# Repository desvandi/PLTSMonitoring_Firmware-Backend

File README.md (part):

# PLTS Monitoring — Firmware, Backend GAS, & Toolkit

**Firmware Version:** v1.9.3 · **Backend GAS:** WAVE-7+ · **License:** MIT
**Status:** Development (v1.9.x INA219 dynamic gain switching — hardware acceptance pending; v1.9.3 menutup REL-03/REL-04: build kini reproducible)
**Repositori kembar (PWA frontend):** [desvandi/PLTSMonitoring_PWA](https://github.com/desvandi/PLTSMonitoring_PWA)

---

## Daftar Isi

1. [Gambaran Proyek](#1-gambaran-proyek)
2. [Arsitektur Sistem](#2-arsitektur-sistem)
3. [Struktur Repositori](#3-struktur-repositori)
4. [Hardware Requirements](#4-hardware-requirements)
5. [Firmware v1.9.x — INA219 Dynamic Gain Switching](#5-firmware-v19x--ina219-dynamic-gain-switching)
6. [Panduan Deployment Lengkap](#6-panduan-deployment-lengkap)
7. [Konfigurasi Firmware](#7-konfigurasi-firmware)
8. [Backend Google Apps Script](#8-backend-google-apps-script)
9. [CI/CD Pipeline](#9-cicd-pipeline)
10. [Release Engineering](#10-release-engineering)
11. [Hardware Acceptance](#11-hardware-acceptance)
12. [Testing](#12-testing)
13. [Troubleshooting](#13-troubleshooting)
14. [Changelog](#14-changelog)

---

## 1. Gambaran Proyek

Proyek ini adalah sistem monitoring PLTS (Pembangkit Listrik Tenaga Surya) berbasis ESP32 untuk baterai 48V LiFePO4. Sistem mencakup telemetri lengkap (tegangan, arus, daya, SOC, suhu, BMS), alarm real-time, kontrol relay 8-channel, OTA update dengan signature verification, dan push notification.

### Dua Subsistem

| Subsistem | Fungsi | Komponen |
|-----------|--------|----------|
| **PLTS Monitor** (dasbor) | Telemetri → Google Apps Script → PWA Next.js; realtime MQTT opsional | `firmware/`, `firmware-generic/`, `code.gs/`, `scripts/` |
| **Push-Alarm MonitorIoT** | Alarm sensor via Web Push terenkripsi (VAPID + aes128gcm) | `push-alarm/` |

### Prinsip Inti

- **Never fabricate certainty** — setiap pengukuran membawa `value/unit/quality/source/timestamp`; sensor gagal → `null` (bukan `0`)
- **Fail-closed** — production build menolak konfigurasi tanpa signature/CA/allowlist
- **Immutable releases** — setiap release ditandatangani GPG + Ed25519, provenance binding machine-verifiable

---

## 2. Arsitektur Sistem

```
┌─────────────────────────────────────────────────────────────┐
│                     ESP32-WROOM-32                          │
│                                                             │
│  ┌──────────┐  ┌──────────┐  ┌──────────┐  ┌──────────┐   │
│  │ INA219   │  │ ADC GPIO │  │ SHT31    │  │ PCF8574  │   │
│  │ (Arus)   │  │ (Tegang) │  │ (Suhu)   │  │ (Relay)  │   │
│  └────┬─────┘  └────┬─────┘  └────┬─────┘  └────┬─────┘   │
│       │ I²C         │ ADC         │ I²C         │ I²C      │
│  ┌────┴─────────────┴─────────────┴─────────────┴────┐    │
│  │              Firmware v1.9.3                      │    │
│  │  • Dynamic PGA Switching (±80mV / ±160mV)        │    │
│  │  • Voltage Divider 190kΩ/10kΩ (20:1)             │    │
│  │  • 8-Channel Relay Controller (E-WAVE)           │    │
│  │  • Reproducible Build (deterministic identity)   │    │
│  │  • OTA Manager (Ed25519 + SHA-256)               │    │
│  │  • MQTT TLS / HTTPS telemetry                    │    │
│  └───────────────────┬──────────────────────────────┘    │
│                      │                                    │
└──────────────────────┼────────────────────────────────────┘
                       │
              ┌────────┴────────┐
              │   WiFi / MQTT   │
              └────────┬────────┘
                       │
          ┌────────────┴────────────┐
          │                         │
    ┌─────┴─────┐           ┌──────┴──────┐
    │  HTTPS    │           │   MQTT TLS  │
    │  POST     │           │  (opsional) │
    └─────┬─────┘           └──────┬──────┘
          │                        │
    ┌─────┴────────────────────────┴─────┐
    │     Google Apps Script (Backend)    │
    │  • Telemetry ingest (HMAC auth)     │
    │  • Google Sheets logging            │
    │  • Telegram alerts                 │
    │  • OTA command dispatch             │
    └─────────────┬───────────────────────┘
                  │
           ┌──────┴──────┐
           │  PWA (Vercel) │
           │  Next.js 16   │
           └───────────────┘
```

### Topologi Operasi

| Topologi | Transport | Backend | Use Case |
|----------|-----------|--------|----------|
| **A (Dasbor)** | HTTPS POST | Google Apps Script + Google Sheets | Standby/standalone tanpa internet real-time |
| **B (Realtime)** | MQTT TLS | Broker MQTT + PWA subscribe | Real-time dashboard dengan live updates |

---

## 3. Struktur Repositori

```
PLTSMonitoring_Firmware-Backend/
├── firmware/                    # Modular production firmware (v1.9.3)
│   ├── Core/                    #   Config.h, Types.h, Globals.h, Common.h
│   ├── Drivers/                 #   INA219, ADC, SHT31, ACS712, PCF8574, RTC
│   ├── Services/                #   OtaManager, RelayController, AlarmRegistry, dll
│   ├── Network/                 #   MQTT transport, telemetry publisher, OTA handler
│   ├── Web/                     #   HTTP server, REST handlers (status, OTA, config, dll)
│   ├── Storage/                 #   NVS config store, filesystem
│   ├── Utils/                   #   Crypto (Ed25519), CRC, I2C recovery, JSON
│   ├── AI/                      #   GasAdvisor (HMAC-signed AI insights)
│   ├── Comm/                    #   BMS protocols (CAN, Modbus RTU/TCP)
│   ├── firmware_v1.ino          #   Main entry point
│   ├── platformio.ini           #   Build configs: development, staging, production
│   └── partitions_ota_1mb5.csv  #   OTA partition table
│
├── firmware-generic/            # Generic firmware (ESP Web Tools flashing)
│   ├── src/
│   │   └── plts_firmware_v1.ino #   Single-file firmware (same features, simpler build)
│   ├── manifest.json            #   ESP Web Tools manifest (v1.9.3)
│   ├── platformio.ini
│   └── bin/                     #   CI-built binaries (gitignored)
│
├── code.gs/                     # Google Apps Script backend
│   └── Code.gs                  #   doPost handler, telemetry ingest, HMAC, OTA dispatch
│
├── push-alarm/                  # MonitorIoT Push-Alarm subsystem
│   ├── gas/                     #   GAS Web Push core (Code.gs, WebPushCore.gs)
│   ├── firmware/                #   Alarm firmware (MonitorIoT_Firmware.ino)
│   ├── tools/                   #   VAPID key gen, deploy config, audit tools
│   └── tests/                   #   Cross-audit, smoke, webpush-core tests
│
├── scripts/                     # Release engineering + testing
│   ├── sign_firmware.py         #   Ed25519 firmware signing
│   ├── generate_provenance.py   #   Release provenance (release.json, provenance.json)
│   ├── generate_canonical_manifest.py  # Schema 2.0 OTA manifest
│   ├── generate_provenance_binding.py  # Explicit provenance chain
│   ├── release_gate.py          #   Master release gate (strict mode)
│   ├── release_firmware_generic.py    # Generic tree release builder
│   ├── verify_tag_signature.py  #   GPG tag verification (P0-1)
│   ├── verify_hardware_acceptance.py  # HW acceptance gate (P0-2)
│   ├── verify_ota_evidence.py   #   OTA physical test gate
│   ├── verify_ina219_hardware_acceptance.py  # INA219 HW acceptance (v1.9.x)
│   ├── decode_ina219_config.py  #   INA219 register decoder (canonical)
│   ├── test_ina219_config_registers.py  # INA219 register unit test
│   ├── test_*.py / test_*.js    #   30+ test scripts (unit, property, contract, bench)
│   └── ...
│
├── docs/                        #   Hanya data fungsional (dibaca skrip/CI)
│   ├── hardware-revisions.json  #     Registry revisi hardware (verify_ota_evidence dkk.)
│   ├── hardware-acceptance/     #   Evidence + template verifikasi (release gate P0-2)
│   │   ├── v1.8.0.json          #     Filled-in evidence (verdict=PASS)
│   │   ├── v1.8.0.template.json #     Template v1.8.0
│   │   ├── v1.9.2.template.json #     Template v1.9.2
│   │   └── v1.9.3.template.json #     Template v1.9.3 (REL-03: SHA byte-exact evidence)
│   └── ota-physical-test/       #   Template uji fisik OTA (verify_ota_evidence)
│       ├── v1.8.0.template.json
│       └── v1.9.3.template.json
│
├── .github/workflows/
│   └── build-firmware.yml       #   CI: test → build → sign → gate → tag-verify → hw-verify → release
│
└── README.md                    # File ini
```

---

## 4. Hardware Requirements

### Komponen Utama

| Komponen | Spesifikasi | Fungsi |
|----------|-------------|--------|
| **ESP32-WROOM-32** | Dual-core 240MHz, 4MB Flash, WiFi+BT | Mikrokontroler utama |
| **INA219** | I²C 0x40, shunt 100A/75mV (R=0.75mΩ) | Pengukuran arus baterai (1A–150A) |
| **Shunt Resistor** | 100A/75mV (0.75mΩ) | Low-side current sensing |
| **Voltage Divider** | R1=190kΩ, R2=10kΩ (ratio 20:1) + 0.1µF cap | Pembacaan tegangan baterai 42–57.5V via ADC |
| **SHT31** | I²C, ±0.3°C, ±2%RH | Suhu + kelembaban ambient |
| **PCF8574** | I²C expander 8-bit | 8-channel relay control |
| **Relay Module** | 8-channel, active-LOW optocoupler | Kontrol beban PLTS |
| **Emergency Relay** | Active-LOW, normally-closed E-stop | Safety cutoff (hardware-level) |
| **ACS712-30A** (opsional) | ADC GPIO35 | Arus AC inverter |
| **PZEM-004T** (opsional) | Modbus RTU | Meter AC presisi |

### Wiring INA219 (Low-Side Sensing)

```
Baterai (+) ──────────────────────────────────────── Beban (+)
                                              │
                                         [Divider]
                                         R1=190kΩ
                                              │
Baterai (−) ──────┬──────────────────────┬───── ADC GPIO34
                  │                      │
              [Shunt 100A]              R2=10kΩ
              75mV, 0.75mΩ               │
                  │                   [0.1µF]
                  ├──── INA219 Vin+      │
                  │                      │
                  └──── INA219 Vin−      │
                  │                      │
                 GND ────────────────────┘
```

> **Penting:** R100 (0.1Ω) bawaan modul INA219 **wajib dicopot**. Gunakan shunt eksternal 100A/75mV. INA219 dipasang low-side (jalur GND) karena Vbus bisa 57.5V > 26V max INA219.

### Pin Assignment

| GPIO | Fungsi | Modul |
|------|--------|-------|
| 21 | I²C SDA | INA219, SHT31, PCF8574 |
| 22 | I²C SCL | INA219, SHT31, PCF8574 |
| 34 | ADC1 CH6 | Voltage divider (input-only, WiFi-safe) |
| 35 | ADC1 CH7 | ACS712 AC current (opsional) |
| 0 | BOOT button | Factory reset trigger |
| 2 | Built-in LED | Status indicator |

---

## 5. Firmware v1.9.x — INA219 Dynamic Gain Switching

### Masalah

Rentang arus PLTS sangat lebar: 1A (standby) hingga 150A (beban puncak). Single PGA range INA219 tidak bisa cover keduanya:
- **±80mV**: saturasi di ~106A (150A × 0.75mΩ = 112.5mV > 80mV)
- **±160mV**: resolusi buruk di arus standby 1–2A

### Solusi: Dynamic PGA Switching

Firmware v1.9.2+ (termasuk v1.9.3) secara otomatis beralih PGA berdasarkan besaran arus:

| Mode | Register | PGA Range | Max Current | Resolusi |
|------|----------|-----------|-------------|----------|
| Standby | `0x0FFF` | ±80mV (gain /2) | 106A | 10µV/bit (0.013A) |
| Peak | `0x17FF` | ±160mV (gain /4) | 213A | 10µV/bit |

### Hysteresis

```
|I| < 90A   → ±80mV  (high-resolution standby)
|I| ≥ 100A  → ±160mV (peak load, no saturation)
```
Gap 10A mencegah chattering saat beban hover di sekitar threshold.

### INA219 Config Register (TI Datasheet SBOS448G)

```
Bit 15    : RST (1 = reset)
Bit 14    : RESERVED (must be 0)
Bit 13    : BRNG (0 = 16V FSR, 1 = 32V FSR)
Bits 12:11: PG (00=±40mV, 01=±80mV, 10=±160mV, 11=±320mV)
Bits 10:7 : BADC (4-bit, 1111 = 12-bit/128-sample/68ms)
Bits 6:3  : SADC (4-bit, 1111 = 12-bit/128-sample/68ms)
Bits 2:0  : MODE (111 = shunt+bus continuous)
```

### Safety Features

1. **Register readback verification** — setiap PGA switch diverifikasi via I²C readback
2. **Sample discard** — sample pertama setelah PGA switch dibuang (settling time 68ms)
3. **Saturation detection** — di ±80mV mode, jika shunt > 78mV → emergency switch ke ±160mV
4. **pga_mode telemetry** — field `bat.pgaMode` ("80mV"/"160mV") dikirim ke backend + PWA

### Verifikasi Register

```bash
python3 scripts/decode_ina219_config.py 0x0FFF 0x17FF
python3 scripts/test_ina219_config_registers.py
```

---

## 6. Panduan Deployment Lengkap

### Prasyarat

- **PlatformIO Core** 6.1.18+ (`pip install platformio`)
- **Python** 3.11+ (untuk scripts)
- **Git** dengan GPG signing configured
- **Google Account** (untuk Apps Script + Sheets)
- **Vercel Account** (untuk PWA deployment — lihat repo PWA)

### Langkah 1: Clone Repositori

```bash
git clone https://github.com/desvandi/PLTSMonitoring_Firmware-Backend.git
cd PLTSMonitoring_Firmware-Backend
```

### Langkah 2: Build Firmware

#### Opsi A: Modular Production (Recommended)

```bash
cd firmware

# Set production secrets (WAJIB sebelum build production)
export MQTT_BROKER_HOST="your-broker.example.com"
export MQTT_BROKER_PORT="8883"
export MQTT_USERNAME="plts-device"
export MQTT_PASSWORD="your-password"
export MQTT_ROOT_CA="$(cat roots.pem)"
export OTA_ED25519_PUBLIC_KEY_HEX="your-64-hex-char-public-key"
export OTA_HTTPS_ROOT_CA="$(cat ota-ca.pem)"

# Build
pio run -e production

# Output: .pio/build/production/firmware.bin
```

#### Opsi B: Development (tanpa secrets)

```bash
cd firmware
pio run -e development
```

#### Opsi C: Generic (ESP Web Tools browser flashing)

```bash
cd firmware-generic
pio run -e esp32dev
# Output: bin/plts_firmware_v1.9.3.bin
```

### Langkah 3: Sign Firmware (Ed25519)

```bash
# Generate keypair (sekali saja)
python3 scripts/sign_firmware.py --gen-keys
# Output: firmware_signing_private.pem + firmware_signing_public.pem

# Sign binary
python3 scripts/sign_firmware.py --sign .pio/build/production/firmware.bin
# Output: firmware.bin.sig (128 hex chars = 64 bytes Ed25519)

# Verify
python3 scripts/sign_firmware.py --verify firmware.bin.sig firmware.bin
```

### Langkah 4: Flash ke ESP32

#### Via USB (PlatformIO)

```bash
cd firmware
pio run -e production -t upload
# Monitor:
pio device monitor -b 115200
```

#### Via ESP Web Tools (Browser)

1. Host `firmware-generic/bin/` di web server (GitHub Pages, Vercel, dll)
2. Buka PWA → Setup → "Install Firmware" button
3. Browser akan flash via Web Serial API

### Langkah 5: Deploy Backend Google Apps Script

1. Buka [script.google.com](https://script.google.com) → New Project
2. Copy seluruh isi `code.gs/Code.gs` ke editor
3. Buat Google Sheet baru, copy ID dari URL
4. Di Apps Script, jalankan `setupMasterTemplate()` (Run → function)
5. Set `AUTH_TOKEN` di Config sheet (minimal 16 karakter, tidak boleh "CHANGE_ME")
6. Deploy → New Deployment → Web App
   - Execute as: Me
   - Who has access: Anyone
7. Copy Web App URL → simpan untuk konfigurasi PWA

### Langkah 6: Generate OTA Signing Keys

```bash
# Generate Ed25519 keypair untuk OTA
python3 scripts/sign_firmware.py --gen-keys

# Public key hex (untuk firmware Config.h / OTA_ED25519_PUBLIC_KEY_HEX)
xxd -p -c 64 firmware_signing_public.pem | head -1
# Atau:
python3 -c "
from cryptography.hazmat.primitives import serialization
key = open('firmware_signing_public.pem','rb').read()
pub = serialization.load_pem_public_key(key)
raw = pub.public_bytes(serialization.Encoding.Raw, serialization.PublicFormat.Raw)
print(raw.hex())
"
```

### Langkah 7: Konfigurasi ESP32 (via PWA)

1. Buka PWA di browser (deploy dari repo PWA)
2. Hubungkan ke WiFi AP ESP32 ("PLTS-Setup-XXXX")
3. PWA akan redirect ke setup page
4. Isi: WiFi SSID+password, GAS URL, AUTH_TOKEN, MQTT broker (opsional)
5. Submit → ESP32 reboot → connect ke WiFi

### Langkah 8: Verifikasi

1. Buka Serial Monitor: `pio device monitor -b 115200`
2. Verifikasi log INA219:
   ```
   [INA219 0x40] config readback OK: 0x0FFF (BRNG=0 16V, PGA=1 ±80mV, BADC=15, SADC=15, MODE=7)
   [INA219 0x40] init: shunt=0.7500 mΩ, cal=0x..., sign=-1.0, pga=80mV
   ```
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
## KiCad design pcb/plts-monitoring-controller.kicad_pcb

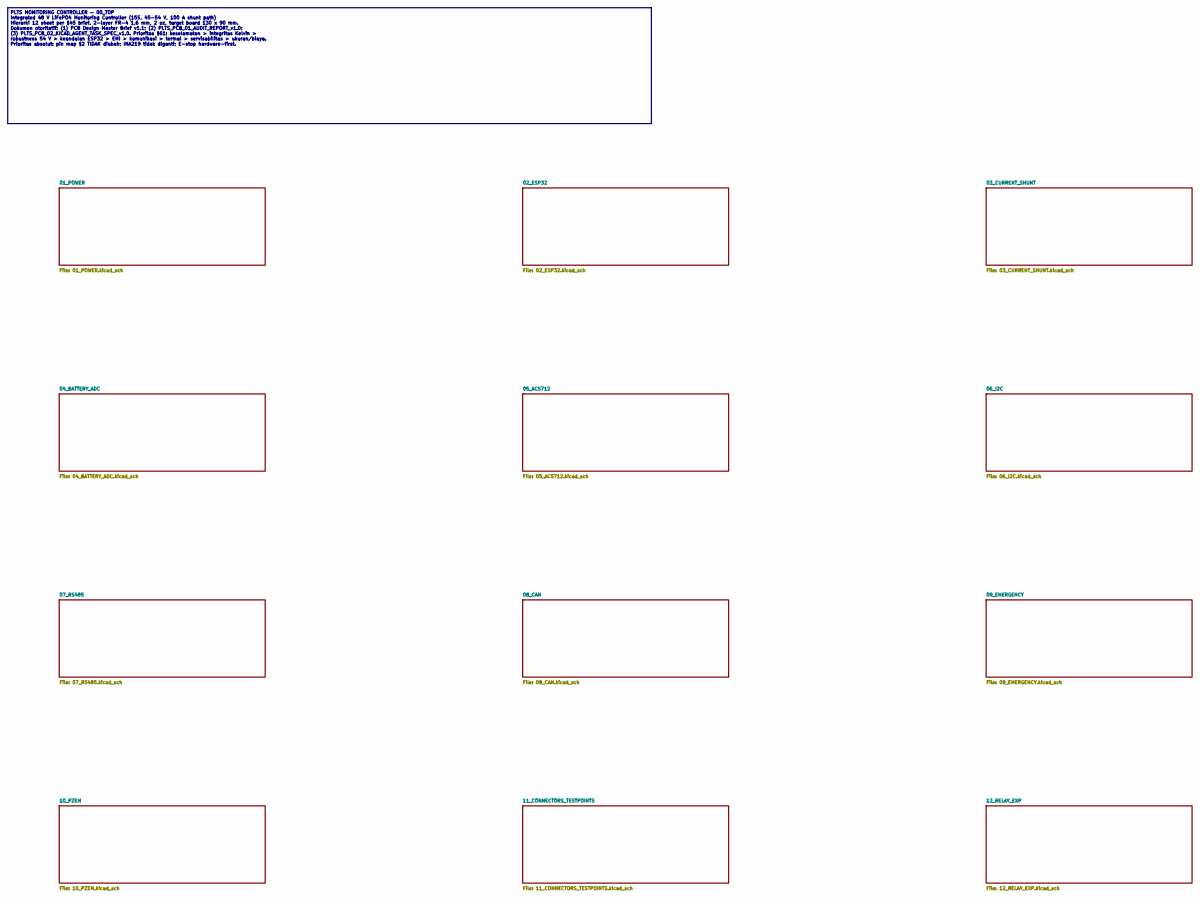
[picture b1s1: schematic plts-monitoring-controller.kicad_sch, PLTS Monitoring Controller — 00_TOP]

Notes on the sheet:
PLTS MONITORING CONTROLLER — 00_TOP Integrated 48 V LiFePO4 Monitoring Controller (15S, 45-54 V, 100 A shunt path) Hierarki 12 sheet per §45 brief. 2-layer FR-4 1,6 mm, 2 oz, target board 130 x 90 mm. Dokumen otoritatif: (1) PCB Design Master Brief v1.1; (2) PLTS_PCB_01_AUDIT_REPORT_v1.0; (3) PLTS_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

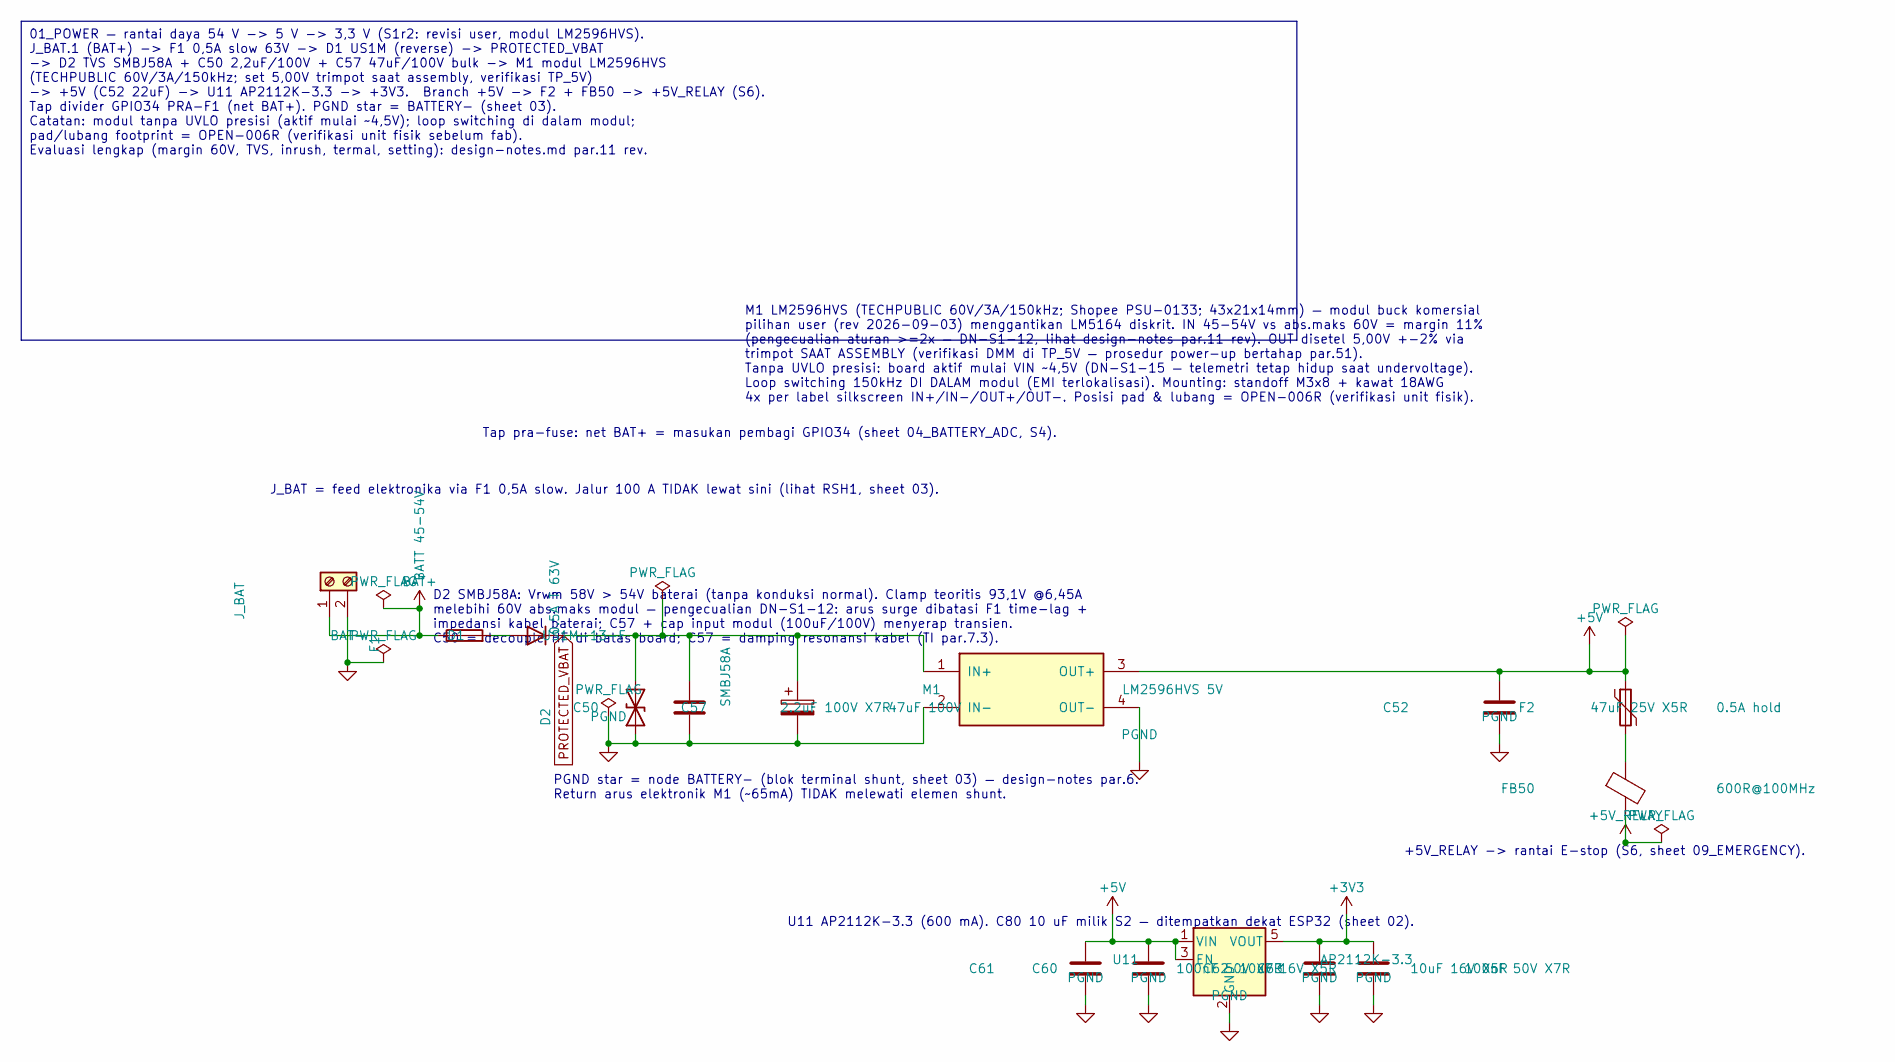
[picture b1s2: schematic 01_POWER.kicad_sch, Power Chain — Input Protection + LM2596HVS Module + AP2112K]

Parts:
C50: 2.2uF 100V X7R; C_1210_3225Metric
C52: 47uF 25V X5R; C_1210_3225Metric
C57: 47uF 100V; CP_Elec_10x10.5
C60, C62: 10uF 16V X5R; C_0805_2012Metric
C61, C63: 100nF 50V X7R; C_0603_1608Metric
D1: US1M-13-F; D_SMA
D2: SMBJ58A; D_SMB
F1: 0.5A T 63V; Fuse_1206_3216Metric
F2: 0.5A hold; Fuse_1812_4532Metric
FB50: 600R@100MHz; L_0805_2012Metric
J_BAT: BATT 45-54V; TerminalBlock_Phoenix_MKDS-1,5-2-5.08_1x02_P5.08mm_Horizont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
M1: LM2596HVS 5V; Module_LM2596HVS
U11: AP2112K-3.3; SOT-23-5

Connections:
+3V3: C62.1, C63.1, U11.5 (VOUT); also elsewhere on the board
+5V: C52.1, C60.1, C61.1, F2.1, M1.3 (OUT+), U11.1 (VIN), U11.3 (EN); also elsewhere on the board
+5V_RELAY: FB50.2; also elsewhere on the board
BAT+: F1.1, J_BAT.1; also elsewhere on the board
BAT-: J_BAT.2; also elsewhere on the board
unnamed: D1.2 (A), F1.2
unnamed: F2.2, FB50.1
PGND: C50.2, C52.2, C57.2, C60.2, C61.2, C62.2, C63.2, D2.1 (A1), M1.2 (IN-), M1.4 (OUT-), U11.2 (GND); also elsewhere on the board
PROTECTED_VBAT: C50.1, C57.1, D1.1 (K), D2.2 (A2), M1.1 (IN+)

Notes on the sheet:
J_BAT = feed elektronika via F1 0,5A slow. Jalur 100 A TIDAK lewat sini (lihat RSH1, sheet 03).
Tap pra-fuse: net BAT+ = masukan pembagi GPIO34 (sheet 04_BATTERY_ADC, S4).
M1 LM2596HVS (TECHPUBLIC 60V/3A/150kHz; Shopee PSU-0133; 43x21x14mm) — modul buck komersial pilihan user (rev 2026-09-03) menggantikan LM5164 diskrit. IN 45-54V vs abs.maks 60V = margin 11% (pengecualian aturan >=2x — DN-S1-12, lihat design-notes par.11 rev). OUT disetel 5,00V +-2% via trimpot SAAT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
D2 SMBJ58A: Vrwm 58V > 54V baterai (tanpa konduksi normal). Clamp teoritis 93,1V @6,45A melebihi 60V abs.maks modul — pengecualian DN-S1-12: arus surge dibatasi F1 time-lag + impedansi kabel baterai; C57 + cap input modul (100uF/100V) menyerap transien. C50 = decouple HF di batas board; C57 = dampi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
PGND star = node BATTERY- (blok terminal shunt, sheet 03) — design-notes par.6. Return arus elektronik M1 (~65mA) TIDAK melewati elemen shunt.
U11 AP2112K-3.3 (600 mA). C80 10 uF milik S2 — ditempatkan dekat ESP32 (sheet 02).
+5V_RELAY -> rantai E-stop (S6, sheet 09_EMERGENCY).
01_POWER — rantai daya 54 V -> 5 V -> 3,3 V (S1r2: revisi user, modul LM2596HVS). J_BAT.1 (BAT+) -> F1 0,5A slow 63V -> D1 US1M (reverse) -> PROTECTED_VBAT -> D2 TVS SMBJ58A + C50 2,2uF/100V + C57 47uF/100V bulk -> M1 modul LM2596HVS (TECHPUBLIC 60V/3A/150kHz; set 5,00V trimpot saat assembly, verif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

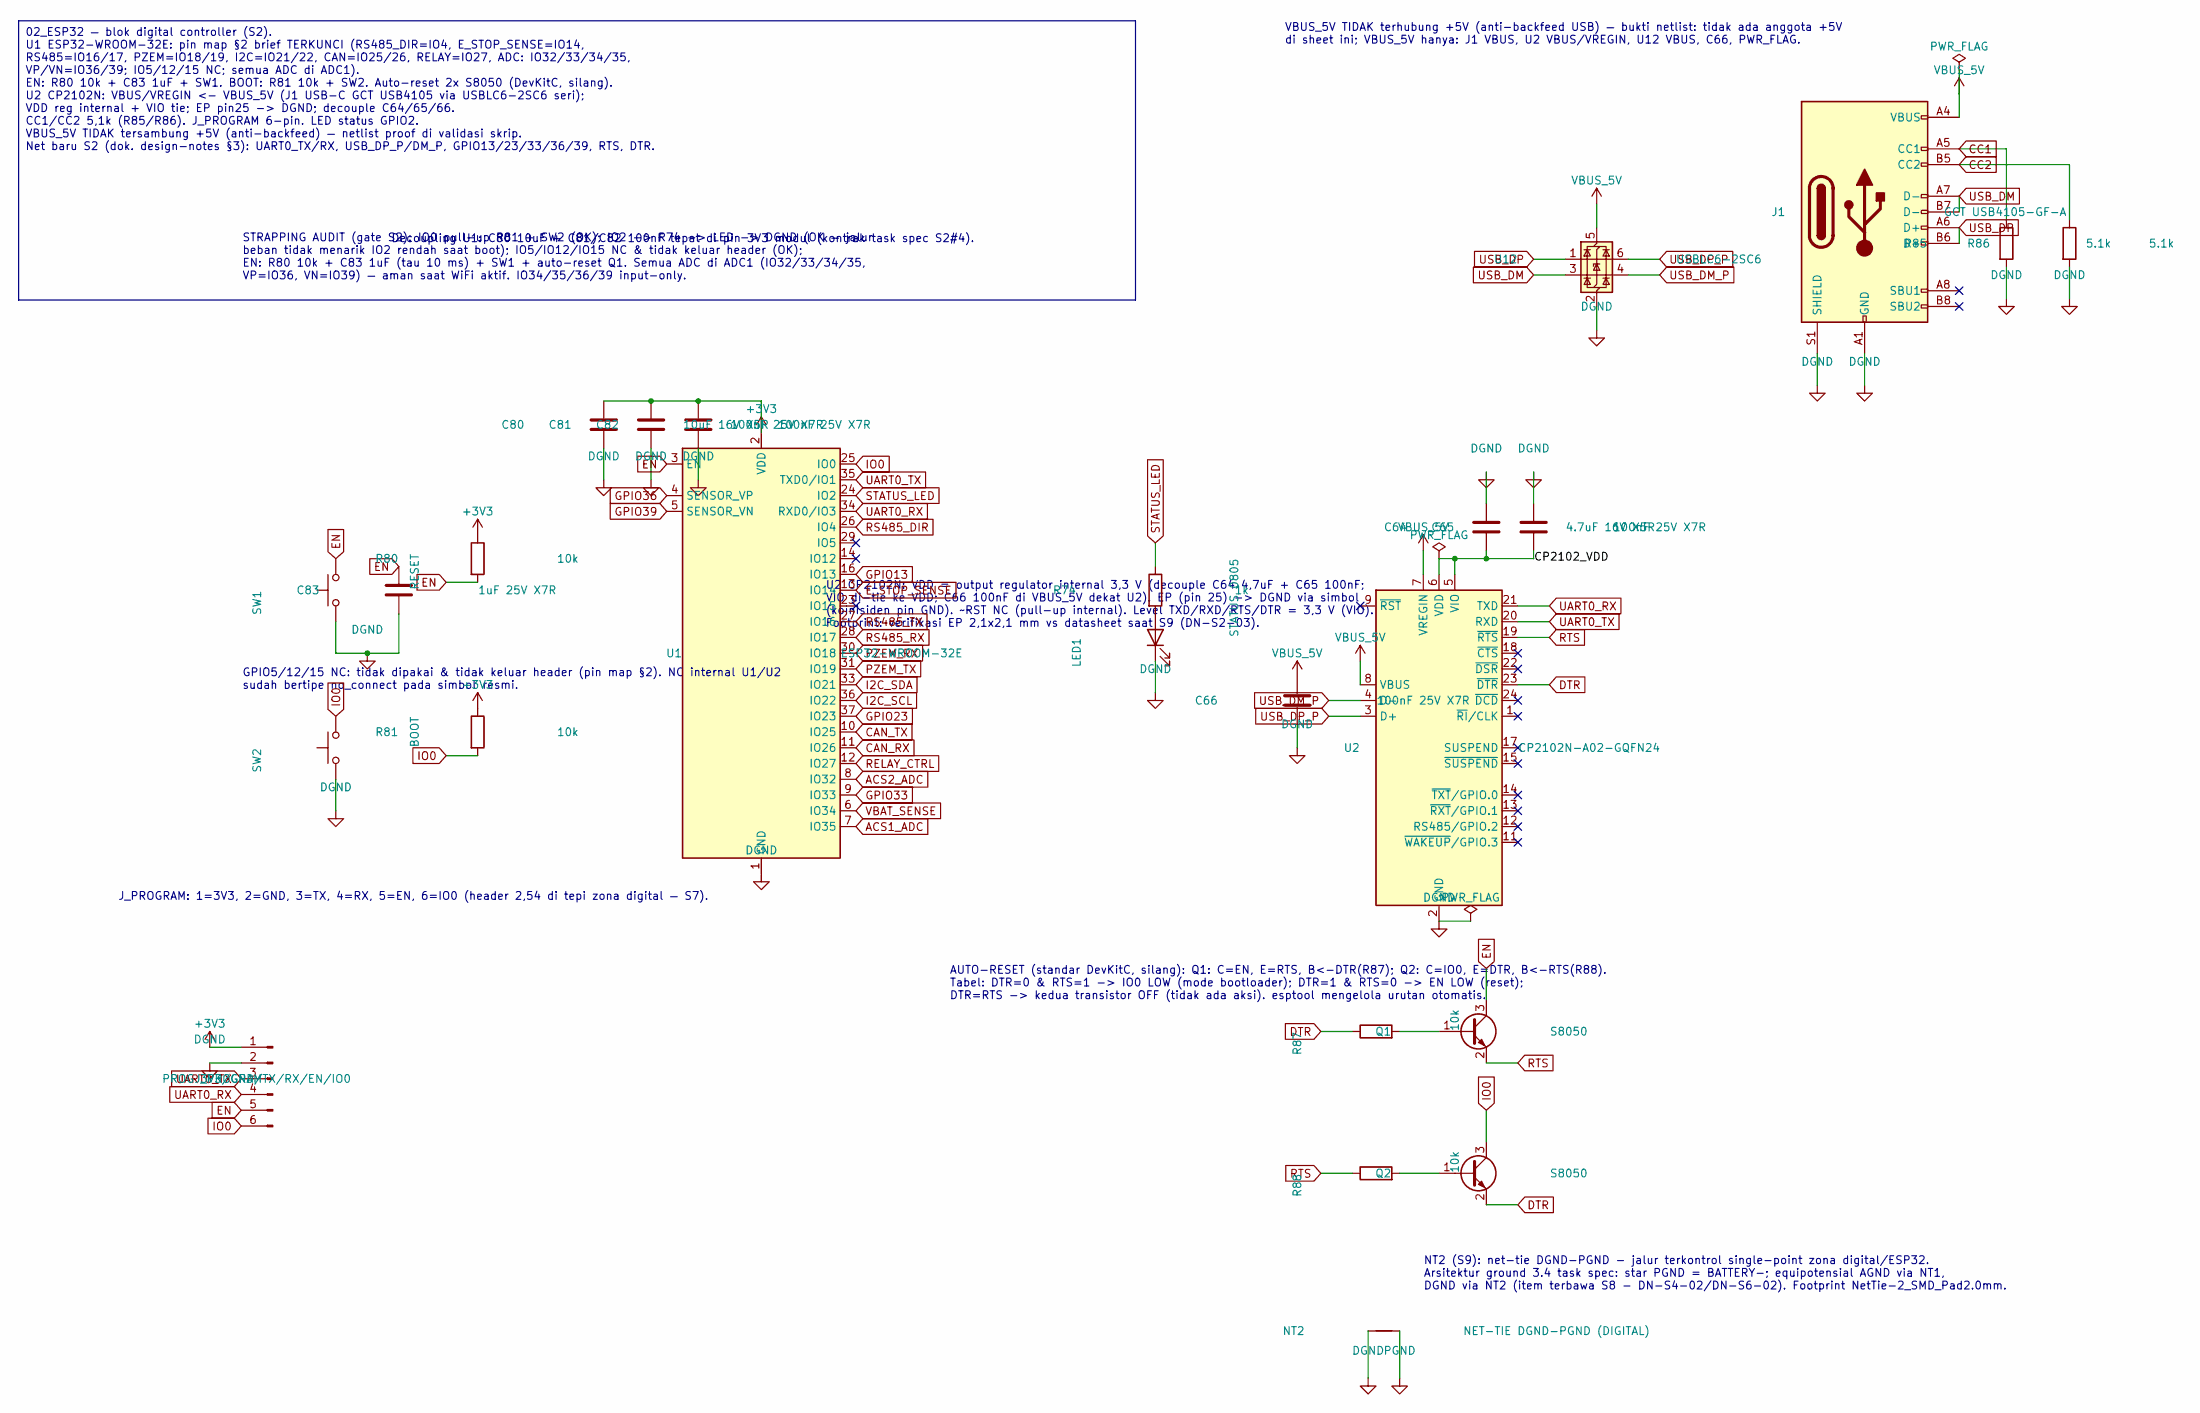
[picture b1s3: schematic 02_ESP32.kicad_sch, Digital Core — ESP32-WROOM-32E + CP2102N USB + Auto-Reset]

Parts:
C64: 4.7uF 16V X5R; C_0805_2012Metric
C65, C66, C81, C82: 100nF 25V X7R; C_0603_1608Metric
C80: 10uF 16V X5R; C_0805_2012Metric
C83: 1uF 25V X7R; C_0603_1608Metric
J1: GCT USB4105-GF-A; USB_C_Receptacle_GCT_USB4105-xx-A_16P_TopMnt_Horizontal
J_PROGRAM: PROG 3V3/GND/TX/RX/EN/IO0; PinHeader_1x06_P2.54mm_Vertical
LED1: STATUS 0805; LED_0805_2012Metric
NT2: NET-TIE DGND-PGND (DIGITAL); NetTie-2_SMD_Pad2.0mm
Q1, Q2: S8050; SOT-23
R74: 1k; R_0603_1608Metric
R80, R81, R87, R88: 10k; R_0603_1608Metric
R85, R86: 5.1k; R_0603_1608Metric
SW1: RESET; SW_PUSH_6mm
SW2: BOOT; SW_PUSH_6mm
U1: ESP32-WROOM-32E
U2: CP2102N-A02-GQFN24; HVQFN-24-1EP_4x4mm_P0.5mm_EP2.1x2.1mm
U12: USBLC6-2SC6; SOT-23-6

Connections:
+3V3: C80.1, C81.1, C82.1, J_PROGRAM.1, R80.1, R81.1, U1.2 (VDD); also elsewhere on the board
/02_ESP32/CP2102_VDD: C64.2, C65.2, U2.5 (VIO), U2.6 (VDD)
ACS1_ADC: U1.7 (IO35); also elsewhere on the board
ACS2_ADC: U1.8 (IO32); also elsewhere on the board
CAN_RX: U1.11 (IO26); also elsewhere on the board
CAN_TX: U1.10 (IO25); also elsewhere on the board
CC1: J1.A5 (CC1), R85.1
CC2: J1.B5 (CC2), R86.1
DGND: C64.1, C65.1, C66.2, C80.2, C81.2, C82.2, C83.2, J1.A1 (GND), J1.A12 (GND), J1.B1 (GND), J1.B12 (GND), J1.S1 (SHIELD), J_PROGRAM.2, LED1.1 (K), NT2.1, R85.2, R86.2, SW1.1, SW2.1, U1.1 (GND), U1.15 (GND), U1.38 (GND), U1.39 (GND), U2.2 (GND), U2.25 (GND), U12.2 (GND); also elsewhere on the board
DTR: Q2.2 (E), R87.1, U2.23 (~DTR)
EN: C83.1, J_PROGRAM.5, Q1.3 (C), R80.2, SW1.2, U1.3 (EN); also elsewhere on the board
E_STOP_SENSE: U1.13 (IO14); also elsewhere on the board
GPIO13: U1.16 (IO13); also elsewhere on the board
GPIO23: U1.37 (IO23); also elsewhere on the board
GPIO33: U1.9 (IO33); also elsewhere on the board
GPIO36: U1.4 (SENSOR_VP); also elsewhere on the board
GPIO39: U1.5 (SENSOR_VN); also elsewhere on the board
I2C_SCL: U1.36 (IO22); also elsewhere on the board
I2C_SDA: U1.33 (IO21); also elsewhere on the board
IO0: J_PROGRAM.6, Q2.3 (C), R81.2, SW2.2, U1.25 (IO0); also elsewhere on the board
unnamed: LED1.2 (A), R74.2
unnamed: Q1.1 (B), R87.2
unnamed: Q2.1 (B), R88.2
PGND: NT2.2; also elsewhere on the board
PZEM_RX: U1.30 (IO18); also elsewhere on the board
PZEM_TX: U1.31 (IO19); also elsewhere on the board
RELAY_CTRL: U1.12 (IO27); also elsewhere on the board
RS485_DIR: U1.26 (IO4); also elsewhere on the board
RS485_RX: U1.28 (IO17); also elsewhere on the board
RS485_TX: U1.27 (IO16); also elsewhere on the board
RTS: Q1.2 (E), R88.1, U2.19 (~RTS)
STATUS_LED: R74.1, U1.24 (IO2)
UART0_RX: J_PROGRAM.4, U1.34 (RXD0/IO3), U2.21 (TXD); also elsewhere on the board
UART0_TX: J_PROGRAM.3, U1.35 (TXD0/IO1), U2.20 (RXD); also elsewhere on the board
USB_DM: J1.A7 (D-), J1.B7 (D-), U12.3 (I/O2)
USB_DM_P: U2.4 (D-), U12.4 (I/O2)
USB_DP: J1.A6 (D+), J1.B6 (D+), U12.1 (I/O1)
USB_DP_P: U2.3 (D+), U12.6 (I/O1)
VBAT_SENSE: U1.6 (IO34); also elsewhere on the board
VBUS_5V: C66.1, J1.A4 (VBUS), J1.A9 (VBUS), J1.B4 (VBUS), J1.B9 (VBUS), U2.7 (VREGIN), U2.8 (VBUS), U12.5 (VBUS)

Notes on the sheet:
STRAPPING AUDIT (gate S2): IO0 pull-up R81 + SW2 (OK); IO2 -> R74 -> LED -> DGND (OK — jalur beban tidak menarik IO2 rendah saat boot); IO5/IO12/IO15 NC & tidak keluar header (OK); EN: R80 10k + C83 1uF (tau 10 ms) + SW1 + auto-reset Q1. Semua ADC di ADC1 (IO32/33/34/35, VP=IO36, VN=IO39) — aman sa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
AUTO-RESET (standar DevKitC, silang): Q1: C=EN, E=RTS, B<-DTR(R87); Q2: C=IO0, E=DTR, B<-RTS(R88). Tabel: DTR=0 & RTS=1 -> IO0 LOW (mode bootloader); DTR=1 & RTS=0 -> EN LOW (reset); DTR=RTS -> kedua transistor OFF (tidak ada aksi). esptool mengelola urutan otomatis.
VBUS_5V TIDAK terhubung +5V (anti-backfeed USB) — bukti netlist: tidak ada anggota +5V di sheet ini; VBUS_5V hanya: J1 VBUS, U2 VBUS/VREGIN, U12 VBUS, C66, PWR_FLAG.
U2 CP2102N: VDD = output regulator internal 3,3 V (decouple C64 4,7uF + C65 100nF; VIO di-tie ke VDD; C66 100nF di VBUS_5V dekat U2). EP (pin 25) -> DGND via simbol (koinisiden pin GND). ~RST NC (pull-up internal). Level TXD/RXD/RTS/DTR = 3,3 V (VIO). Footprint: verifikasi EP 2,1x2,1 mm vs datashee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
Decoupling U1: C80 10uF + C81/C82 100nF tepat di pin 3V3 modul (kontrak task spec S2#4).
J_PROGRAM: 1=3V3, 2=GND, 3=TX, 4=RX, 5=EN, 6=IO0 (header 2,54 di tepi zona digital — S7).
GPIO5/12/15 NC: tidak dipakai & tidak keluar header (pin map §2). NC internal U1/U2 sudah bertipe no_connect pada simbol resmi.
02_ESP32 — blok digital controller (S2). U1 ESP32-WROOM-32E: pin map §2 brief TERKUNCI (RS485_DIR=IO4, E_STOP_SENSE=IO14, RS485=IO16/17, PZEM=IO18/19, I2C=IO21/22, CAN=IO25/26, RELAY=IO27, ADC: IO32/33/34/35, VP/VN=IO36/39; IO5/12/15 NC; semua ADC di ADC1). EN: R80 10k + C83 1uF + SW1. BOOT: R81 10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
NT2 (S9): net-tie DGND-PGND - jalur terkontrol single-point zona digital/ESP32. Arsitektur ground 3.4 task spec: star PGND = BATTERY-; equipotensial AGND via NT1, DGND via NT2 (item terbawa S8 - DN-S4-02/DN-S6-02). Footprint NetTie-2_SMD_Pad2.0mm.

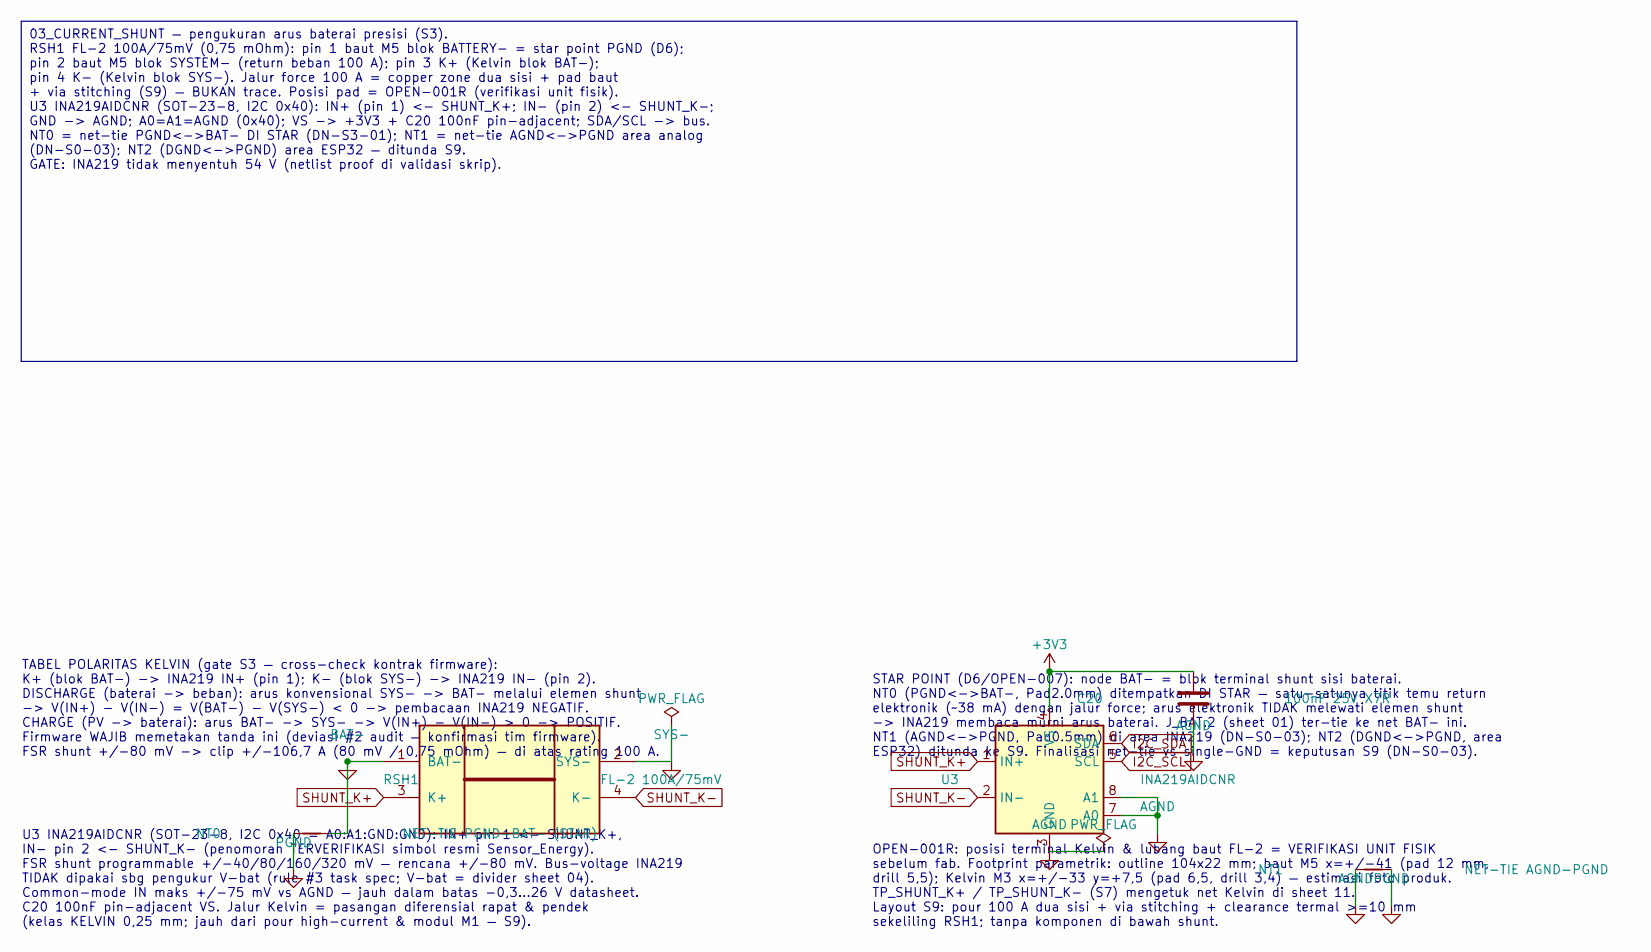
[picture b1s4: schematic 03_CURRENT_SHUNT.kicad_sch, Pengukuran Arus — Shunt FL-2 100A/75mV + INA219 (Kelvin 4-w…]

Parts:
C20: 100nF 25V X7R; C_0603_1608Metric
NT0: NET-TIE PGND-BAT- (STAR); NetTie-2_SMD_Pad2.0mm
NT1: NET-TIE AGND-PGND; NetTie-2_SMD_Pad0.5mm
RSH1: FL-2 100A/75mV; Shunt_FL2_100A
U3: INA219AIDCNR; SOT-23-8

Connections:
+3V3: C20.1, U3.4 (VS); also elsewhere on the board
AGND: C20.2, NT1.1, U3.3 (GND), U3.7 (A0), U3.8 (A1); also elsewhere on the board
BAT-: NT0.2, RSH1.1 (BAT-); also elsewhere on the board
I2C_SCL: U3.5 (SCL); also elsewhere on the board
I2C_SDA: U3.6 (SDA); also elsewhere on the board
PGND: NT0.1, NT1.2; also elsewhere on the board
SHUNT_K+: RSH1.3 (K+), U3.1 (IN+); also elsewhere on the board
SHUNT_K-: RSH1.4 (K-), U3.2 (IN-); also elsewhere on the board
SYS-: RSH1.2 (SYS-)

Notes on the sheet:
TABEL POLARITAS KELVIN (gate S3 — cross-check kontrak firmware): K+ (blok BAT-) -> INA219 IN+ (pin 1); K- (blok SYS-) -> INA219 IN- (pin 2). DISCHARGE (baterai -> beban): arus konvensional SYS- -> BAT- melalui elemen shunt -> V(IN+) - V(IN-) = V(BAT-) - V(SYS-) < 0 -> pembacaan INA219 NEGATIF. CHAR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
STAR POINT (D6/OPEN-007): node BAT- = blok terminal shunt sisi baterai. NT0 (PGND<->BAT-, Pad2.0mm) ditempatkan DI STAR — satu-satunya titik temu return elektronik (~38 mA) dengan jalur force; arus elektronik TIDAK melewati elemen shunt -> INA219 membaca murni arus baterai. J_BAT.2 (sheet 01) ter-t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
U3 INA219AIDCNR (SOT-23-8, I2C 0x40 = A0:A1:GND:GND): IN+ pin 1 <- SHUNT_K+, IN- pin 2 <- SHUNT_K- (penomoran TERVERIFIKASI simbol resmi Sensor_Energy). FSR shunt programmable +/-40/80/160/320 mV — rencana +/-80 mV. Bus-voltage INA219 TIDAK dipakai sbg pengukur V-bat (rule #3 task spec; V-bat = div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
OPEN-001R: posisi terminal Kelvin & lubang baut FL-2 = VERIFIKASI UNIT FISIK sebelum fab. Footprint parametrik: outline 104x22 mm; baut M5 x=+/-41 (pad 12 mm, drill 5,5); Kelvin M3 x=+/-33 y=+7,5 (pad 6,5, drill 3,4) — estimasi foto produk. TP_SHUNT_K+ / TP_SHUNT_K- (S7) mengetuk net Kelvin di shee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
03_CURRENT_SHUNT — pengukuran arus baterai presisi (S3). RSH1 FL-2 100A/75mV (0,75 mOhm): pin 1 baut M5 blok BATTERY- = star point PGND (D6); pin 2 baut M5 blok SYSTEM- (return beban 100 A); pin 3 K+ (Kelvin blok BAT-); pin 4 K- (Kelvin blok SYS-). Jalur force 100 A = copper zone dua sisi + pad bau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

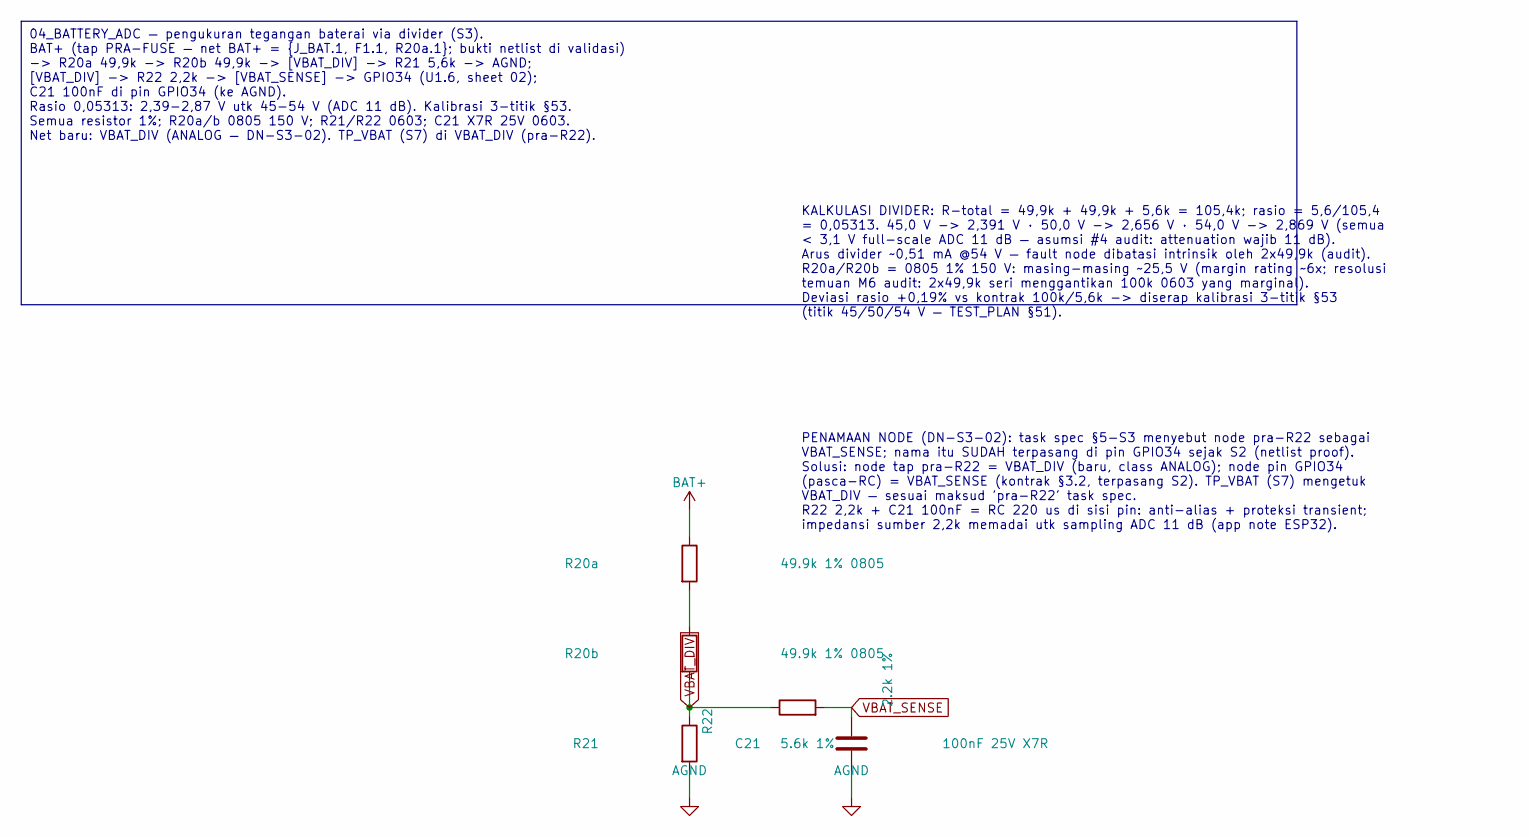
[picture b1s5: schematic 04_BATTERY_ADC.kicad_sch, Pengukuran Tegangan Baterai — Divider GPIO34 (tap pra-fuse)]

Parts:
C21: 100nF 25V X7R; C_0603_1608Metric
R20a, R20b: 49.9k 1% 0805; R_0805_2012Metric
R21: 5.6k 1%; R_0603_1608Metric
R22: 2.2k 1%; R_0603_1608Metric

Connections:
AGND: C21.2, R21.2; also elsewhere on the board
BAT+: R20a.1; also elsewhere on the board
unnamed: R20a.2, R20b.1
VBAT_DIV: R20b.2, R21.1, R22.1; also elsewhere on the board
VBAT_SENSE: C21.1, R22.2; also elsewhere on the board

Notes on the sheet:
KALKULASI DIVIDER: R-total = 49,9k + 49,9k + 5,6k = 105,4k; rasio = 5,6/105,4 = 0,05313. 45,0 V -> 2,391 V · 50,0 V -> 2,656 V · 54,0 V -> 2,869 V (semua < 3,1 V full-scale ADC 11 dB — asumsi #4 audit: attenuation wajib 11 dB). Arus divider ~0,51 mA @54 V — fault node dibatasi intrinsik oleh 2x49,9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
PENAMAAN NODE (DN-S3-02): task spec §5-S3 menyebut node pra-R22 sebagai VBAT_SENSE; nama itu SUDAH terpasang di pin GPIO34 sejak S2 (netlist proof). Solusi: node tap pra-R22 = VBAT_DIV (baru, class ANALOG); node pin GPIO34 (pasca-RC) = VBAT_SENSE (kontrak §3.2, terpasang S2). TP_VBAT (S7) mengetuk 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
04_BATTERY_ADC — pengukuran tegangan baterai via divider (S3). BAT+ (tap PRA-FUSE — net BAT+ = {J_BAT.1, F1.1, R20a.1}; bukti netlist di validasi) -> R20a 49,9k -> R20b 49,9k -> [VBAT_DIV] -> R21 5,6k -> AGND; [VBAT_DIV] -> R22 2,2k -> [VBAT_SENSE] -> GPIO34 (U1.6, sheet 02); C21 100nF di pin GPIO3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

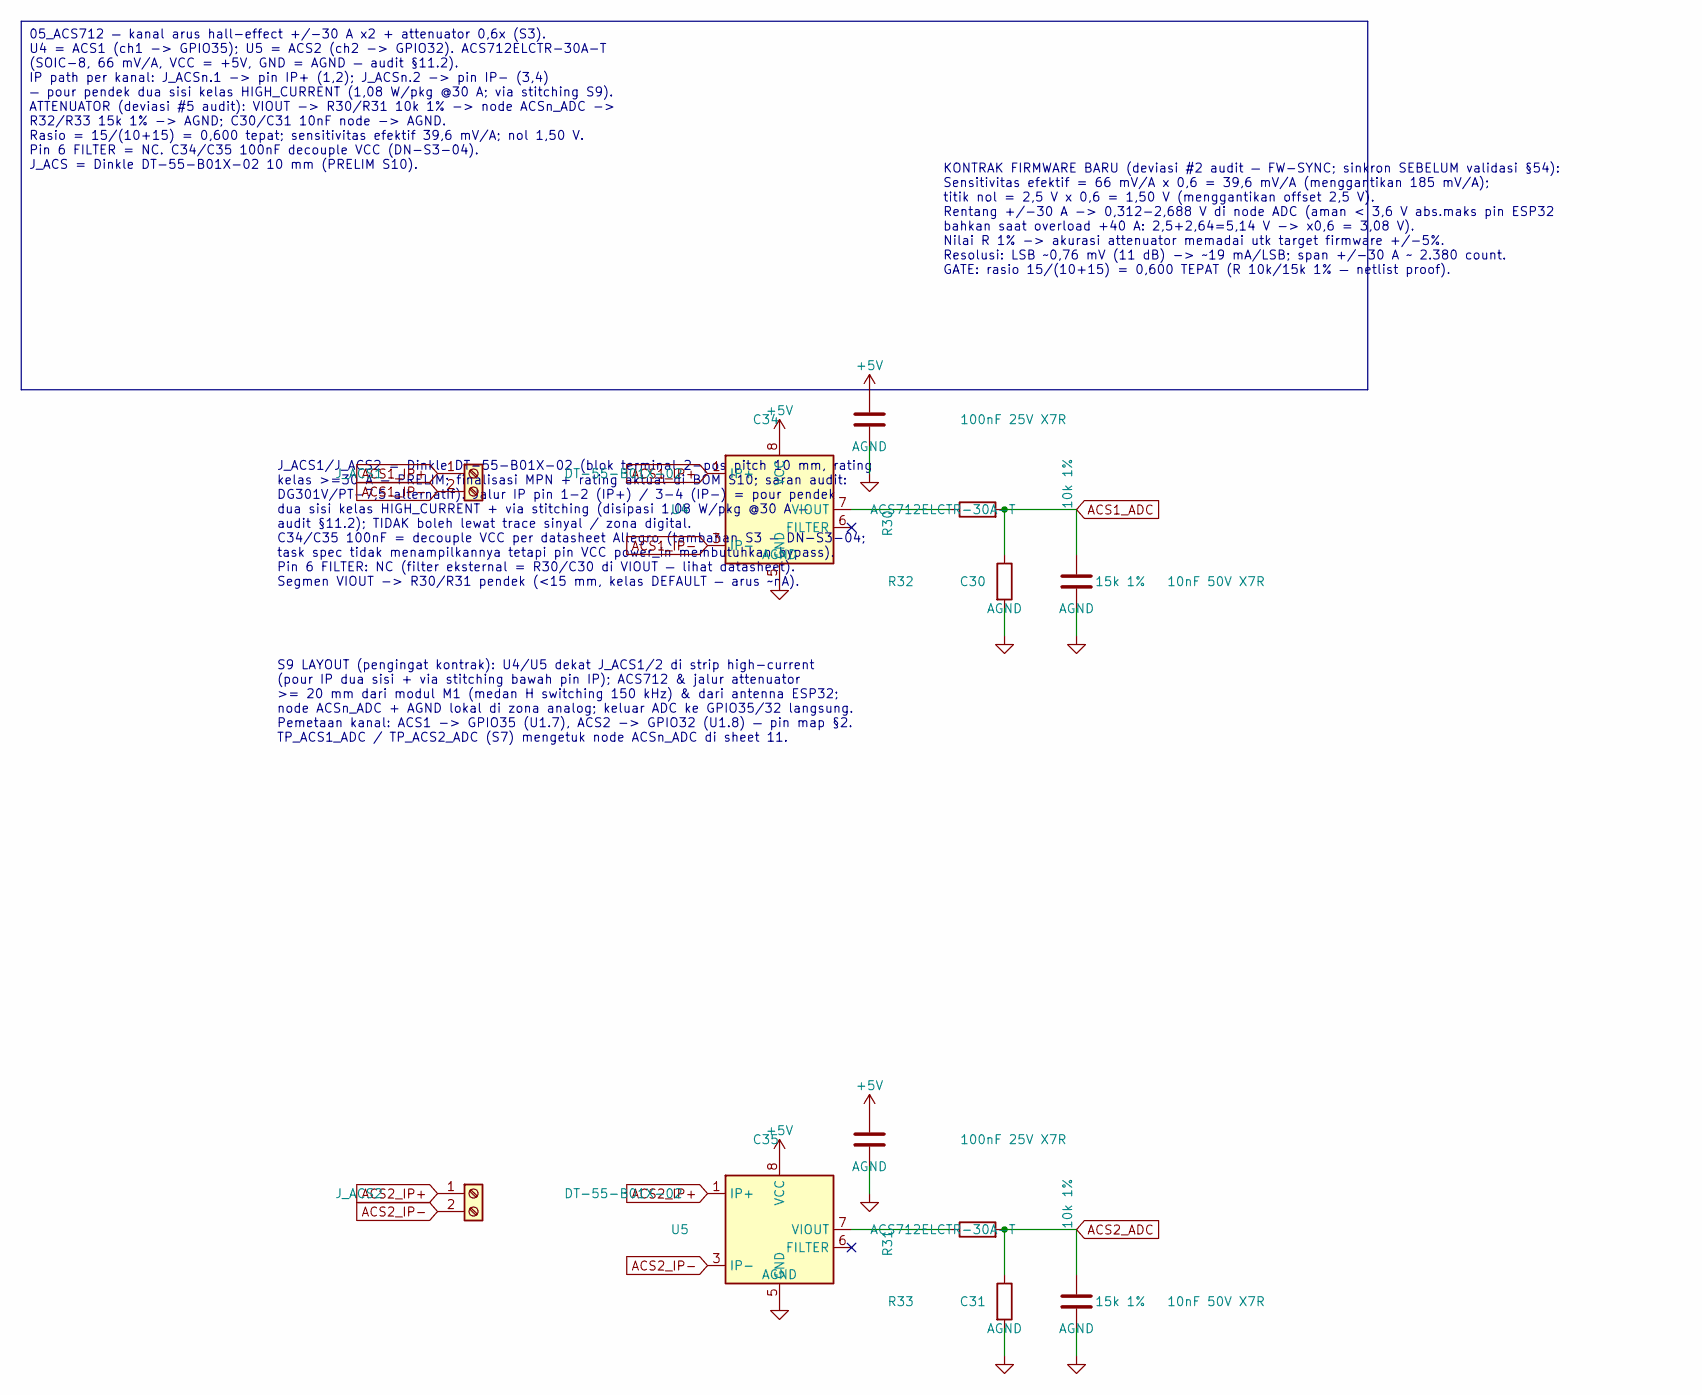
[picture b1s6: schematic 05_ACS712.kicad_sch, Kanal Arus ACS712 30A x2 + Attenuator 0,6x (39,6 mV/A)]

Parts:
C30, C31: 10nF 50V X7R; C_0603_1608Metric
C34, C35: 100nF 25V X7R; C_0603_1608Metric
J_ACS1, J_ACS2: DT-55-B01X-02; TerminalBlock_Dinkle_DT-55-B01X-02_P10.00mm
R30, R31: 10k 1%; R_0603_1608Metric
R32, R33: 15k 1%; R_0603_1608Metric
U4, U5: ACS712ELCTR-30A-T; SOIC-8_3.9x4.9mm_P1.27mm

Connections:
+5V: C34.1, C35.1, U4.8 (VCC), U5.8 (VCC); also elsewhere on the board
ACS1_ADC: C30.1, R30.2, R32.1; also elsewhere on the board
ACS1_IP+: J_ACS1.1, U4.1 (IP+), U4.2 (IP+)
ACS1_IP-: J_ACS1.2, U4.3 (IP-), U4.4 (IP-)
ACS2_ADC: C31.1, R31.2, R33.1; also elsewhere on the board
ACS2_IP+: J_ACS2.1, U5.1 (IP+), U5.2 (IP+)
ACS2_IP-: J_ACS2.2, U5.3 (IP-), U5.4 (IP-)
AGND: C30.2, C31.2, C34.2, C35.2, R32.2, R33.2, U4.5 (GND), U5.5 (GND); also elsewhere on the board
unnamed: R30.1, U4.7 (VIOUT)
unnamed: R31.1, U5.7 (VIOUT)

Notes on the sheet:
KONTRAK FIRMWARE BARU (deviasi #2 audit — FW-SYNC; sinkron SEBELUM validasi §54): Sensitivitas efektif = 66 mV/A x 0,6 = 39,6 mV/A (menggantikan 185 mV/A); titik nol = 2,5 V x 0,6 = 1,50 V (menggantikan offset 2,5 V). Rentang +/-30 A -> 0,312-2,688 V di node ADC (aman < 3,6 V abs.maks pin ESP32 bah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
J_ACS1/J_ACS2 = Dinkle DT-55-B01X-02 (blok terminal 2-pos pitch 10 mm, rating kelas >=30 A — PRELIM; finalisasi MPN + rating aktual di BOM S10; saran audit: DG301V/PT-7,5 alternatif). Jalur IP pin 1-2 (IP+) / 3-4 (IP-) = pour pendek dua sisi kelas HIGH_CURRENT + via stitching (disipasi 1,08 W/pkg @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
S9 LAYOUT (pengingat kontrak): U4/U5 dekat J_ACS1/2 di strip high-current (pour IP dua sisi + via stitching bawah pin IP); ACS712 & jalur attenuator >= 20 mm dari modul M1 (medan H switching 150 kHz) & dari antenna ESP32; node ACSn_ADC + AGND lokal di zona analog; keluar ADC ke GPIO35/32 langsung. 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
05_ACS712 — kanal arus hall-effect +/-30 A x2 + attenuator 0,6x (S3). U4 = ACS1 (ch1 -> GPIO35); U5 = ACS2 (ch2 -> GPIO32). ACS712ELCTR-30A-T (SOIC-8, 66 mV/A, VCC = +5V, GND = AGND — audit §11.2). IP path per kanal: J_ACSn.1 -> pin IP+ (1,2); J_ACSn.2 -> pin IP- (3,4) — pour pendek dua sisi kelas 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

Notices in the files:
README.md:
License:
MIT — see [LICENSE](LICENSE)
